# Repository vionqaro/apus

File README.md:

View this project on [CADLAB.io](https://cadlab.io/project/30607). 

# apus

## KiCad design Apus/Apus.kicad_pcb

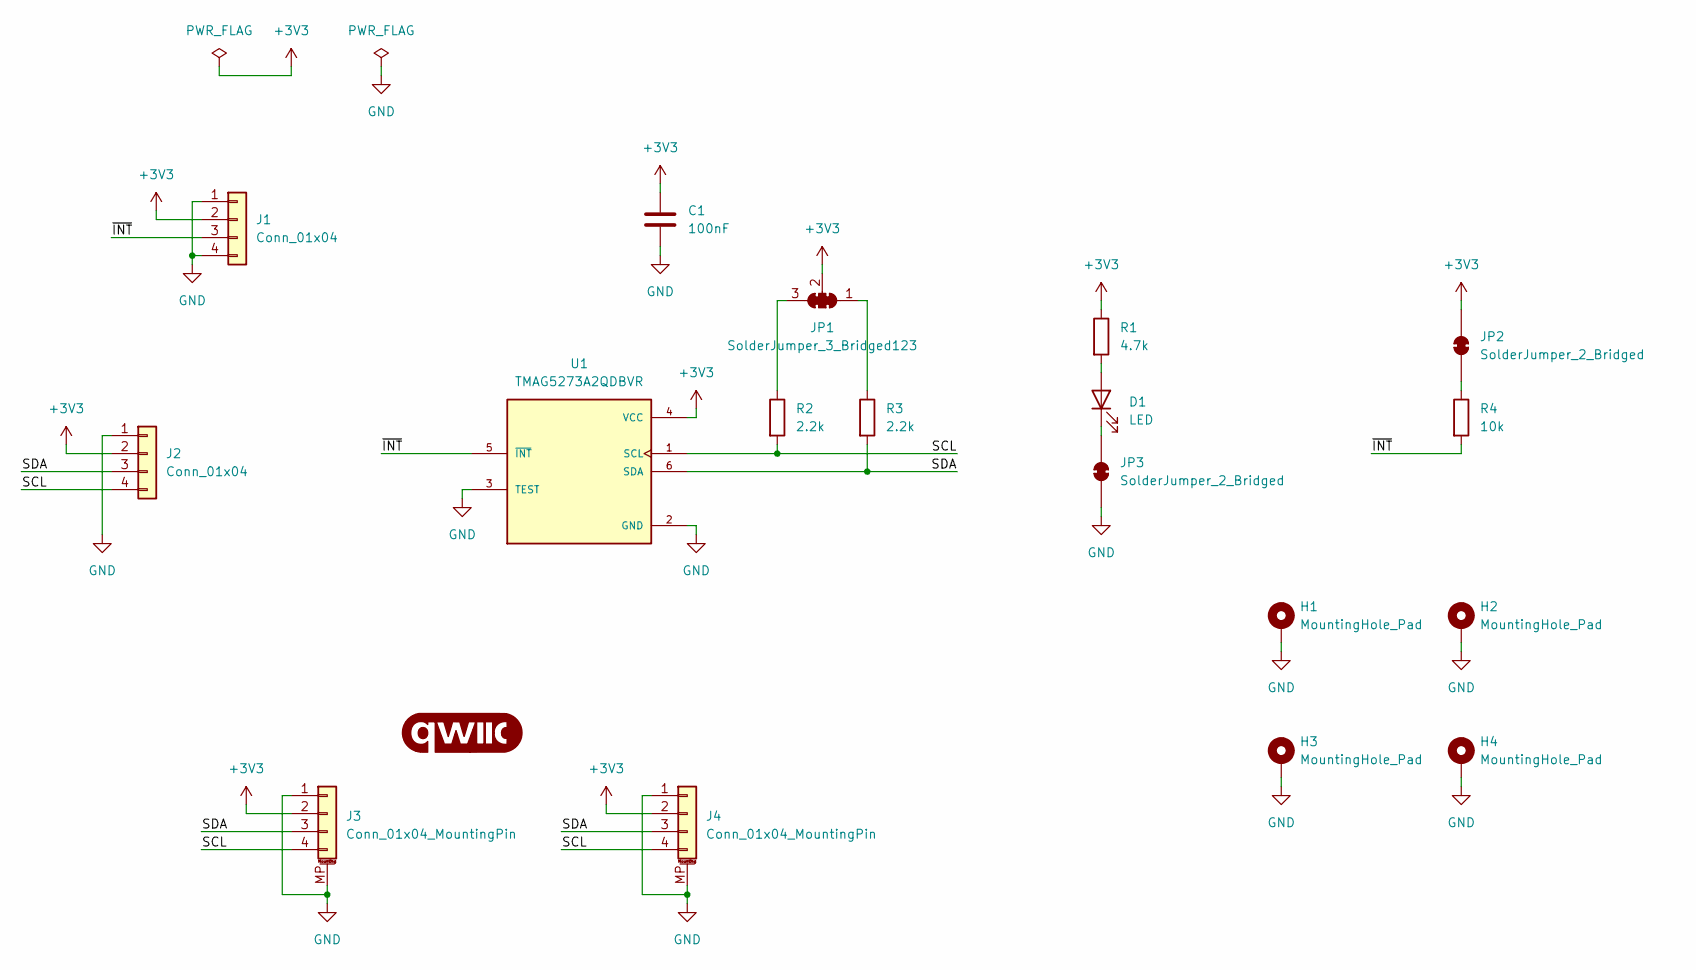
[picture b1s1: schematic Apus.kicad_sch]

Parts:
C1: 100nF; C_0603_1608Metric
D1: LED; LED_0603_1608Metric
G1: qwiic_Logo; TQFP-44_10x10mm_P0.8mm
H1, H2, H3, H4: MountingHole_Pad; MountingHole_3.2mm_M3_Pad
J1, J2: Conn_01x04; PinHeader_1x04_P2.54mm_Vertical
J3, J4: Conn_01x04_MountingPin; JST_SH_SM04B-SRSS-TB_1x04-1MP_P1.00mm_Horizontal
JP1: SolderJumper_3_Bridged123; SolderJumper-3_P1.3mm_Bridged123_RoundedPad1.0x1.5mm_Number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
JP2, JP3: SolderJumper_2_Bridged; SolderJumper-2_P1.3mm_Bridged_RoundedPad1.0x1.5mm
R1: 4.7k; R_0603_1608Metric
R2, R3: 2.2k; R_0603_1608Metric
R4: 10k; R_0603_1608Metric
U1: TMAG5273A2QDBVR; SOT95P280X140-6N; PARTREV B

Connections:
+3V3: C1.1, J1.2, J2.2, J3.2, J4.2, JP1.2 (C), JP2.2 (B), R1.1, U1.4 (VCC)
/SCL: J2.4, J3.4, J4.4, R2.2, U1.1 (SCL)
/SDA: J2.3, J3.3, J4.3, R3.2, U1.6 (SDA)
/~INT: J1.3, R4.2, U1.5 (~INT)
GND: C1.2, H1.1 (1_1), H2.1 (1_1), H3.1 (1_1), H4.1 (1_1), J1.1, J1.4, J2.1, J3.1, J3.MP (MountPin), J4.1, J4.MP (MountPin), JP3.1 (A), U1.2 (GND), U1.3 (TEST)
unnamed: D1.2 (A), R1.2
unnamed: D1.1 (K), JP3.2 (B)
unnamed: JP1.1 (A), R3.1
unnamed: JP1.3 (B), R2.1
unnamed: JP2.1 (A), R4.1

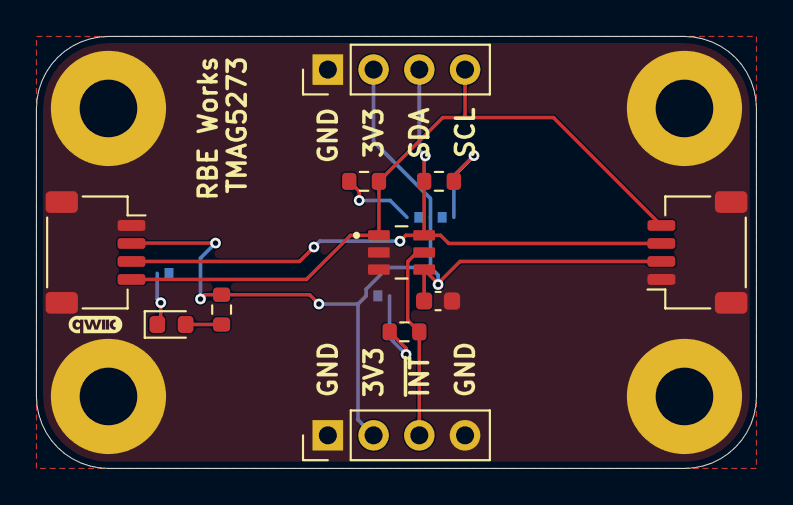
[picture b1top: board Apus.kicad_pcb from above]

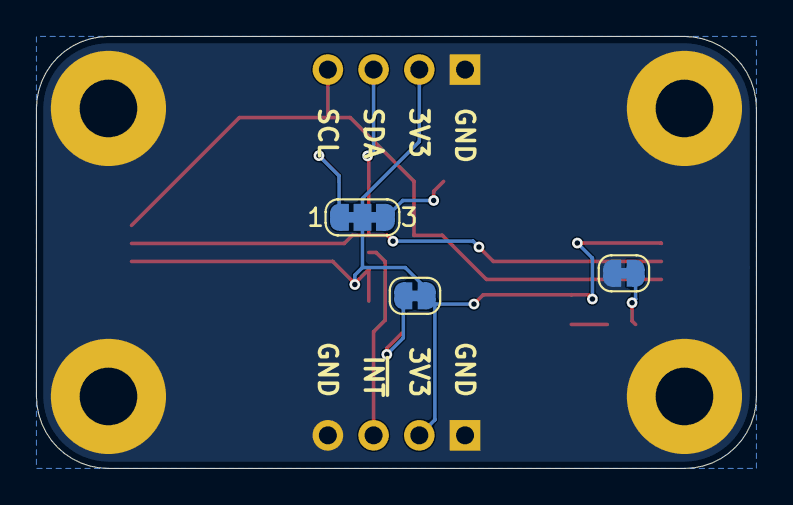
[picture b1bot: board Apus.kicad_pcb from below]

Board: 2 copper layers, 40.0 x 24.0 mm, 18 parts (3 on the bottom side), 10 nets.
